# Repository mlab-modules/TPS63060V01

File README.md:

# MLAB TPS63060V01A Module

The MLAB TPS63060V01A module is based on [TPS63060](https://www.ti.com/lit/ds/symlink/tps63060.pdf?HQS=TI-null-null-digikeymode-df-pf-null-wwe&ts=1614085886440) integrated circuit from Texas Instruments. This circuit is a synchronous step-down (buck-boost) converter, capable of regulating the output voltage whether the input voltage is either higher or lower than the output voltage.

### TPS63060
The TPS63060 is a highly efficient, fully integrated, synchronous buck-boost converter designed for a wide range of applications. This circuit has an internal switching transistor, which allows it to achieve high efficiency at low loads.

The TPS63060 operates in automatic PFM/PWM switching mode, switching between PFM (Pulse Frequency Modulation) mode at low loads for efficiency optimization, and PWM (Pulse Width Modulation) mode at higher loads for better voltage regulation.

### Basic Parameters:
- Input voltage: 2.5 V to 12 V
- Output voltage: 2.5 V to 8 V
- Maximum current for internal transistor: 2 A
- Output voltage selectable at 3.3 V or 5 V (by jumper placement)
- Pin for converter activation: EN
- Pin for power saving mode and synchronization: PS/SYNC

Users can choose between an output voltage of 3.3 V or 5 V using a jumper setting.

A significant feature of the module is the ability to activate and deactivate the converter via the EN (enable input) pin. This is especially useful in applications where power is supplied by batteries, and there is a need to protect them from deep discharge.

A unique feature of the module is also the presence of the PS/SYNC pin, labeled as SN. This allows the power saving mode of the converter to be activated if the current draw is less than 100 mA. This pin can also be used to synchronize the converter with an external clock signal.

## Possible Applications
Due to its range of input and output voltages and the ability to regulate, this module is suitable for various applications. It can be used to power low voltage devices from higher voltage batteries or vice versa. Its versatility makes it suitable for a wide range of devices from mobile devices to IoT applications to industrial systems. The power saving mode and the ability to activate/deactivate the converter also support its use in devices where power consumption efficiency is important.

For more detailed information on the functionality of the TPS63060 circuit, we recommend studying its [technical datasheet](https://www.ti.com/lit/ds/symlink/tps63060.pdf?HQS=TI-null-null-digikeymode-df-pf-null-wwe&ts=1614085886440). If you have any further questions, feel free to contact us via email or [Github discuss page](https://github.com/orgs/MLAB-project/discussions) for more information and resources.

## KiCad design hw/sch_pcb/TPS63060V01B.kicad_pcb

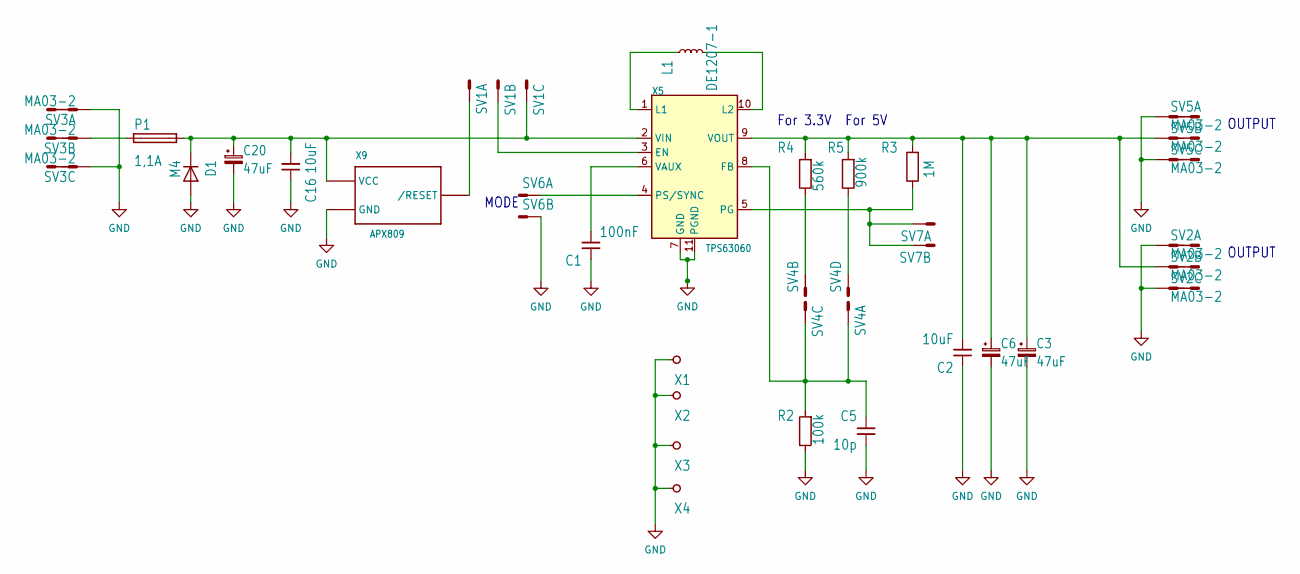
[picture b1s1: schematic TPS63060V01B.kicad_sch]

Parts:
C1: 100nF; C_0805_2012Metric
C2, C16: 10uF; C_0805_2012Metric
C3, C6, C20: 47uF; TantalC_SizeC_Reflow
C5: 10p; C_0805_2012Metric
D1: M4; D_SMA
L1: DE1207-1; DE1205-10
P1: 1,1A; 1812
R2: 100k; R_0805_2012Metric
R3: 1M; R_0805_2012Metric
R4: 560k; R_0805_2012Metric
R5: 900k; R_0805_2012Metric
SV1: MA03-1
SV2, SV3, SV5: MA03-2
SV4: MA02-3; MA02-2
SV6, SV7: MA02-1
X1, X2, X3, X4: SROUB3M; MountingHole_3mm
X5: TPS63060; Texas_S-PWSON-N10_ThermalVias
X9: APX809; SOT23

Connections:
GND: C1.1, C2.1, C3.2, C5.2, C6.2, C16.1, C20.2, D1.2 (A), R2.1, SV2.1 (K), SV2.2 (K), SV2.5 (K), SV2.6 (K), SV3.1 (K), SV3.2 (K), SV3.5 (K), SV3.6 (K), SV5.1 (K), SV5.2 (K), SV5.5 (K), SV5.6 (K), SV6.2, X1.1, X2.1, X3.1, X4.1, X5.7 (GND), X5.11 (PGND), X9.1 (GND)
unnamed: C2.2, C3.1, C6.1, R3.2, R4.2, R5.2, SV2.3 (K), SV2.4 (K), SV5.3 (K), SV5.4 (K), X5.9 (VOUT)
unnamed: C16.2, C20.1, D1.1 (K), P1.2, SV1.3, X5.2 (VIN), X9.3 (VCC)
unnamed: P1.1, SV3.3 (K), SV3.4 (K)
unnamed: R4.1, SV4.2
unnamed: R5.1, SV4.4
unnamed: SV1.1, X9.2 (/RESET)
unnamed: SV1.2, X5.3 (EN)
unnamed: SV6.1, X5.4 (PS/SYNC)
unnamed: R3.1, SV7.1, SV7.2, X5.5 (PG)
unnamed: L1.1, X5.1 (L1)
unnamed: C1.2, X5.6 (VAUX)
unnamed: C5.1, R2.2, SV4.1, SV4.3, X5.8 (FB)
unnamed: L1.2, X5.10 (L2)

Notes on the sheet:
MODE
OUTPUT
For 3.3V
For 5V

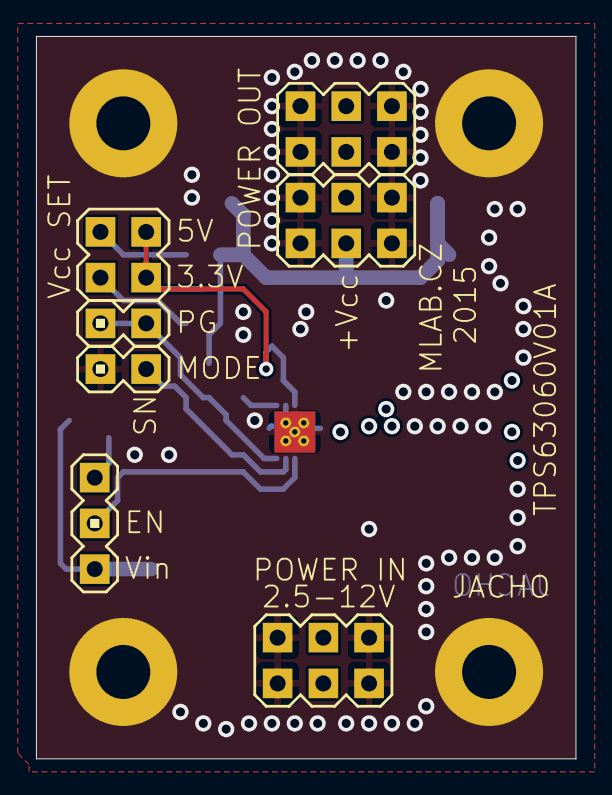
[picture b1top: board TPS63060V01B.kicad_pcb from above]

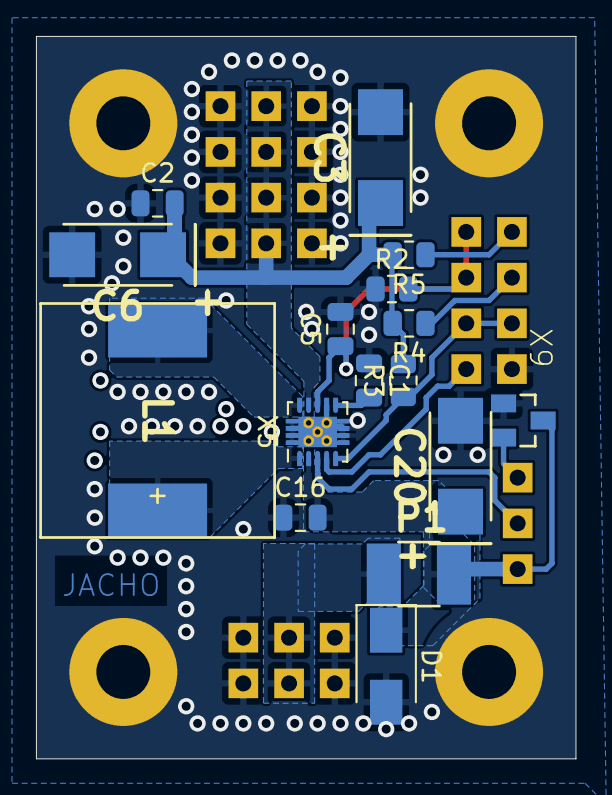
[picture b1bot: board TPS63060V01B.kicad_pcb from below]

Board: 2 copper layers, 30.0 x 40.1 mm, 27 parts (16 on the bottom side), 14 nets.

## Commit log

2017-08-22 rename category folders
2017-08-22 rename files and module folders
2017-08-22 change images path
2017-08-22 create hw folder
2017-08-22 change filepaths
2017-08-22 new .json files
2017-11-16 [MLABweb] 2017-11-16 10:54:11 TPS63060V01A
2018-04-12 [MLABweb] Documentaion edits; TPS63060V01A
2018-11-05 Presun obrazku do slozky img. Pregenerovani dokumentaci.
2021-12-15 Update documentation.
2022-04-06 automated commit; add github actions
2022-04-06 Update actions products
2022-07-20 Prevod modulu z Eagle do KiCad projektu.
2022-07-20 urpava shema a pouzder kvuli prechodu z eagle
2023-05-25 Update metadata files
2023-05-28 Update workflow files
2023-09-16 Update image to image_title
2023-09-16 Update status
